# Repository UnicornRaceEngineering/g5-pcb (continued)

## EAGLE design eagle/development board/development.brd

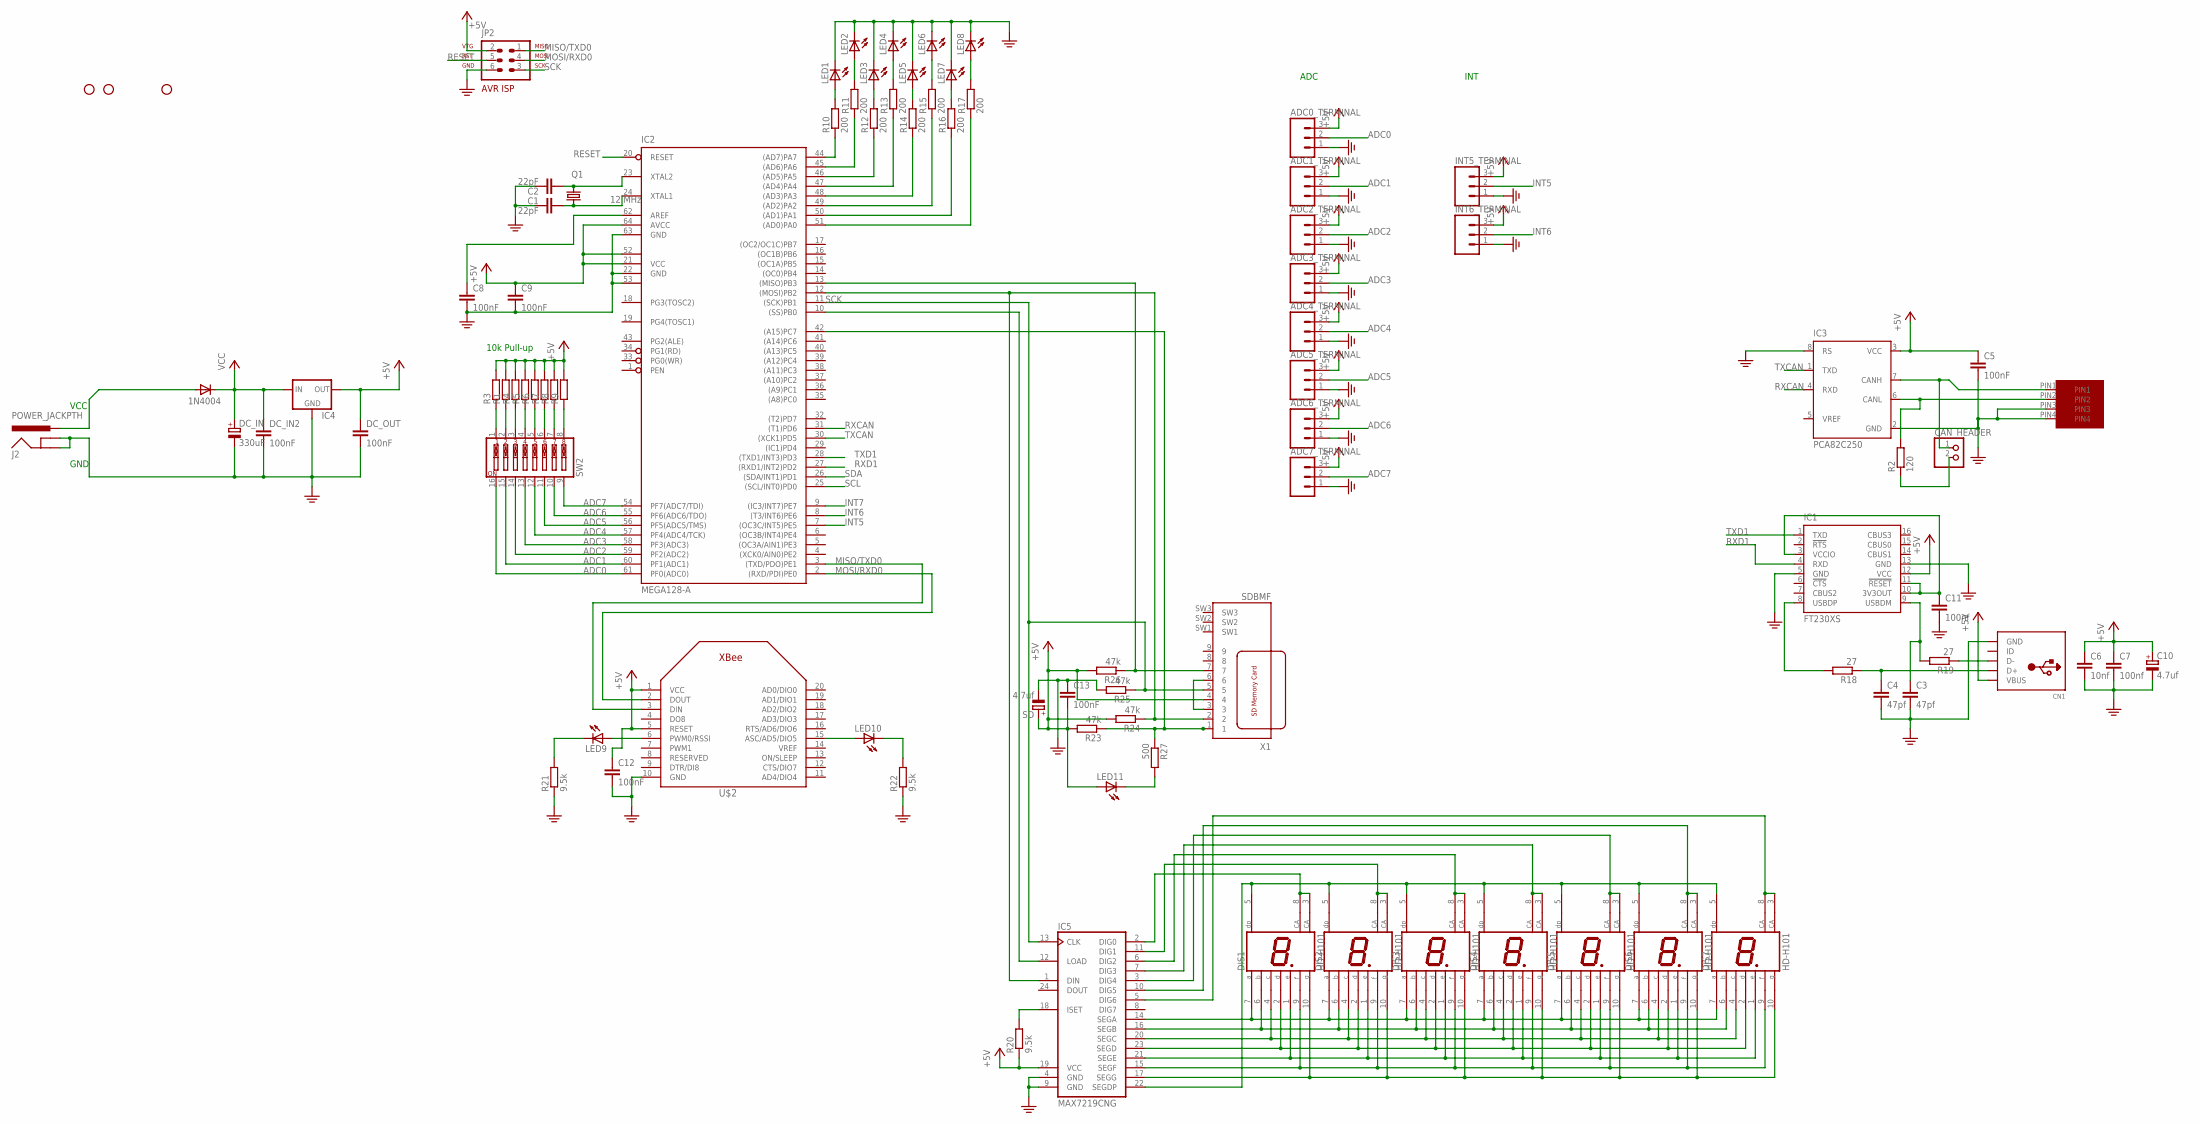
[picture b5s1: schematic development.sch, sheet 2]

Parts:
ADC0_TERMINAL, ADC1_TERMINAL, ADC2_TERMINAL, ADC3_TERMINAL, ADC4_TERMINAL, ADC5_TERMINAL, ADC6_TERMINAL, ADC7_TERMINAL: M03SCREW; SCREWTERMINAL-3.5MM-3
C1, C2: 22pF; C5B2.5
C3, C4: 47pf; C050-025X075
C5, C8, C9, C12, C13: 100nF; C050-024X044
C6: 10nf; C050-025X075
C7, C11: 100nf; C050-025X075
C10: 4.7uf; E2,5-7
CAN_HEADER: PINHD-1X2; 1X02
CN1: USBMINIB; USB-MINIB
DC_IN: 330uF; E15-5
DC_IN2: 100nF; C050-024X044
DC_OUT: 100nF; C050-024X044
DIS1, DIS2, DIS3, DIS4, DIS5, DIS6, DIS7: HD-H101; HDSP-M
ENSRET: 1N4004; DO41-10
IC1: FT230XS; SSOP16
IC2: MEGA128-A; TQFP64
IC3: PCA82C250; DIL08
IC4: V_REG_78XXSIDE; 78XXL
IC5: MAX7219CNG; DIL24-3
INT5_TERMINAL, INT6_TERMINAL: M03SCREW; SCREWTERMINAL-3.5MM-3
J2: POWER_JACKPTH; POWER_JACK_PTH
JP2: AVR-ISP-6
JP3, JP4, JP6: STAND-OFF
LED1, LED2, LED3, LED4, LED5, LED6, LED7, LED8: LED3MM
LED9, LED10, LED11: LED5MM
Q1: 12 MHz; HC49U70
R1, R3, R4, R5, R6, R7, R8, R9: R-EU_R0603; R0603
R2: 120; R0603
R10, R11, R12, R13, R14, R15, R16, R17: 200; R0603
R18, R19: 27; R0603
R20, R21, R22: 9.5k; 0204/7
R23, R24, R25, R26: 47k; 0204/7
R27: 500; 0204/7
SD: 4.7uf; E15-5
SW2: SW_DIP-8; DIPSWITCH-08
U$1: MICROFIT4; MICROFIT4SOCK
U$2: XBEE
X1: SDBMF; SDBMF-009XXBXX2

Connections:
+5V: ADC0_TERMINAL.3, ADC1_TERMINAL.3, ADC2_TERMINAL.3, ADC3_TERMINAL.3, ADC4_TERMINAL.3, ADC5_TERMINAL.3, ADC6_TERMINAL.3, ADC7_TERMINAL.3, C5.1, C6.1, C7.1, C9.1, C10.+, C13.2, CN1.VBUS, DC_OUT.1, IC1.12 (VCC), IC2.21 (VCC), IC2.52 (VCC1), IC2.64 (AVCC), IC3.3 (VCC), IC4.OUT, IC5.19 (VCC), INT5_TERMINAL.3, INT6_TERMINAL.3, JP2.2, LED11.A, R1.2, R3.2, R4.2, R5.2, R6.2, R7.2, R8.2, R9.2, R20.1, R23.2, R24.2, R26.2, SD.+, X1.4
ADC0: ADC0_TERMINAL.2, IC2.61 (PF0(ADC0)), SW2.16
ADC1: ADC1_TERMINAL.2, IC2.60 (PF1(ADC1)), SW2.15
ADC2: ADC2_TERMINAL.2, IC2.59 (PF2(ADC2)), SW2.14
ADC3: ADC3_TERMINAL.2, IC2.58 (PF3(ADC3)), SW2.13
ADC4: ADC4_TERMINAL.2, IC2.57 (PF4(ADC4/TCK)), SW2.12
ADC5: ADC5_TERMINAL.2, IC2.56 (PF5(ADC5/TMS)), SW2.11
ADC6: ADC6_TERMINAL.2, IC2.55 (PF6(ADC6/TDO)), SW2.10
ADC7: ADC7_TERMINAL.2, IC2.54 (PF7(ADC7/TDI)), SW2.9
CANJUMP1: CAN_HEADER.1, IC3.7 (CANH), U$1.PIN1
CANJUMP2: CAN_HEADER.2, R2.1
INT5: IC2.7 ((OC3C/INT5)PE5), INT5_TERMINAL.2
INT6: IC2.8 ((T3/INT6)PE6), INT6_TERMINAL.2
INT7: IC2.9 ((IC3/INT7)PE7)
MISO/TXD0: IC2.3 ((TXD/PDO)PE1), JP2.1, U$2.3 (DIN)
MOSI/RXD0: IC2.2 ((RXD/PDI)PE0), JP2.4, U$2.2 (DOUT)
unnamed: C1.2, IC2.24 (XTAL1), Q1.1
unnamed: C2.2, IC2.23 (XTAL2), Q1.2
unnamed: R1.1, SW2.2
unnamed: R3.1, SW2.1
unnamed: ENSRET.A, J2.PWR
unnamed: IC2.44 ((AD7)PA7), R10.1
unnamed: R4.1, SW2.3
unnamed: LED1.A, R10.2
unnamed: IC2.45 ((AD6)PA6), R11.1
unnamed: C8.1, IC2.62 (AREF)
unnamed: LED2.A, R11.2
unnamed: IC2.46 ((AD5)PA5), R12.1
unnamed: LED3.A, R12.2
unnamed: R5.1, SW2.4
unnamed: R6.1, SW2.5
unnamed: R7.1, SW2.6
unnamed: R8.1, SW2.7
unnamed: IC2.47 ((AD4)PA4), R13.1
unnamed: LED4.A, R13.2
unnamed: R9.1, SW2.8
unnamed: IC2.48 ((AD3)PA3), R14.1
unnamed: LED5.A, R14.2
unnamed: IC2.49 ((AD2)PA2), R15.1
unnamed: IC2.50 ((AD1)PA1), R16.1
unnamed: LED6.A, R15.2
unnamed: LED7.A, R16.2
unnamed: IC2.51 ((AD0)PA0), R17.1
unnamed: LED8.A, R17.2
unnamed: C3.1, IC1.9 (USBDM), R19.2
unnamed: IC1.8 (USBDP), R18.2
unnamed: C4.1, CN1.D+, R18.1
unnamed: CN1.D-, R19.1
unnamed: DIS1.7 (A), DIS2.7 (A), DIS3.7 (A), DIS4.7 (A), DIS5.7 (A), DIS6.7 (A), DIS7.7 (A), IC5.14 (SEGA)
unnamed: DIS1.6 (B), DIS2.6 (B), DIS3.6 (B), DIS4.6 (B), DIS5.6 (B), DIS6.6 (B), DIS7.6 (B), IC5.16 (SEGB)
unnamed: DIS1.4 (C), DIS2.4 (C), DIS3.4 (C), DIS4.4 (C), DIS5.4 (C), DIS6.4 (C), DIS7.4 (C), IC5.20 (SEGC)
unnamed: C11.1, IC1.3 (VCCIO), IC1.10 (3V3OUT), IC1.11 (!RESET)
unnamed: DIS1.2 (D), DIS2.2 (D), DIS3.2 (D), DIS4.2 (D), DIS5.2 (D), DIS6.2 (D), DIS7.2 (D), IC5.23 (SEGD)
unnamed: DIS1.1 (E), DIS2.1 (E), DIS3.1 (E), DIS4.1 (E), DIS5.1 (E), DIS6.1 (E), DIS7.1 (E), IC5.21 (SEGE)
unnamed: DIS1.9 (F), DIS2.9 (F), DIS3.9 (F), DIS4.9 (F), DIS5.9 (F), DIS6.9 (F), DIS7.9 (F), IC5.15 (SEGF)
unnamed: DIS1.10 (G), DIS2.10 (G), DIS3.10 (G), DIS4.10 (G), DIS5.10 (G), DIS6.10 (G), DIS7.10 (G), IC5.17 (SEGG)
unnamed: DIS1.5 (DP), DIS2.5 (DP), DIS3.5 (DP), DIS4.5 (DP), DIS5.5 (DP), DIS6.5 (DP), DIS7.5 (DP), IC5.22 (SEGDP)
unnamed: DIS1.3 (CA), DIS1.8 (CA), IC5.2 (DIG0)
unnamed: DIS2.3 (CA), DIS2.8 (CA), IC5.11 (DIG1)
unnamed: DIS3.3 (CA), DIS3.8 (CA), IC5.6 (DIG2)
unnamed: DIS4.3 (CA), DIS4.8 (CA), IC5.7 (DIG3)
unnamed: DIS5.3 (CA), DIS5.8 (CA), IC5.3 (DIG4)
unnamed: DIS6.3 (CA), DIS6.8 (CA), IC5.10 (DIG5)
unnamed: DIS7.3 (CA), DIS7.8 (CA), IC5.5 (DIG6)
unnamed: LED9.K (C), R21.2
unnamed: IC5.18 (ISET), R20.2
unnamed: IC3.6 (CANL), R2.2, U$1.PIN2
unnamed: LED9.A, U$2.6 (PWM0/RSSI)
unnamed: IC2.10 ((SS)PB0), IC5.12 (LOAD)
unnamed: LED10.A, U$2.15 (ASC/AD5/DIO5)
unnamed: LED10.K (C), R22.2
unnamed: X1.3, X1.6
unnamed: IC2.42 ((A15)PC7), R23.1, R27.1, X1.1
unnamed: IC2.12 ((MOSI)PB2), IC5.1 (DIN), R24.1, X1.2
unnamed: IC2.13 ((MISO)PB3), R26.1, X1.7
unnamed: LED11.K (C), R27.2
PE: ADC0_TERMINAL.1, ADC1_TERMINAL.1, ADC2_TERMINAL.1, ADC3_TERMINAL.1, ADC4_TERMINAL.1, ADC5_TERMINAL.1, ADC6_TERMINAL.1, ADC7_TERMINAL.1, C1.1, C2.1, C3.2, C4.2, C5.2, C6.2, C7.2, C8.2, C9.2, C10.-, C11.2, C12.2, C13.1, CN1.GND, DC_IN.-, DC_IN2.2, DC_OUT.2, IC1.5 (GND), IC1.13 (GND), IC2.22 (GND), IC2.53 (GND1), IC2.63 (GND), IC3.2 (GND), IC3.8 (RS), IC4.GND, IC5.4 (GND), IC5.9 (GND), INT5_TERMINAL.1, INT6_TERMINAL.1, J2.GND, J2.GNDBREAK, JP2.6, LED1.K (C), LED2.K (C), LED3.K (C), LED4.K (C), LED5.K (C), LED6.K (C), LED7.K (C), LED8.K (C), R21.1, R22.1, R25.2, SD.-, U$1.PIN3, U$1.PIN4, U$2.10 (GND)
RESET: IC2.20 (RESET), JP2.5
RXCAN: IC2.31 ((T1)PD6), IC3.4 (RXD)
RXD1: IC1.4 (RXD), IC2.27 ((RXD1/INT2)PD2)
SCK: IC2.11 ((SCK)PB1), IC5.13 (CLK), JP2.3, R25.1, X1.5
SCL: IC2.25 ((SCL/INT0)PD0)
SDA: IC2.26 ((SDA/INT1)PD1)
TXCAN: IC2.30 ((XCK1)PD5), IC3.1 (TXD)
TXD1: IC1.1 (TXD), IC2.28 ((TXD1/INT3)PD3)
VCC: C12.1, DC_IN.+, DC_IN2.1, ENSRET.C, IC4.IN, U$2.1 (VCC), U$2.5 (RESET)

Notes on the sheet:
VCC
GND
ADC
INT
10k Pull-up

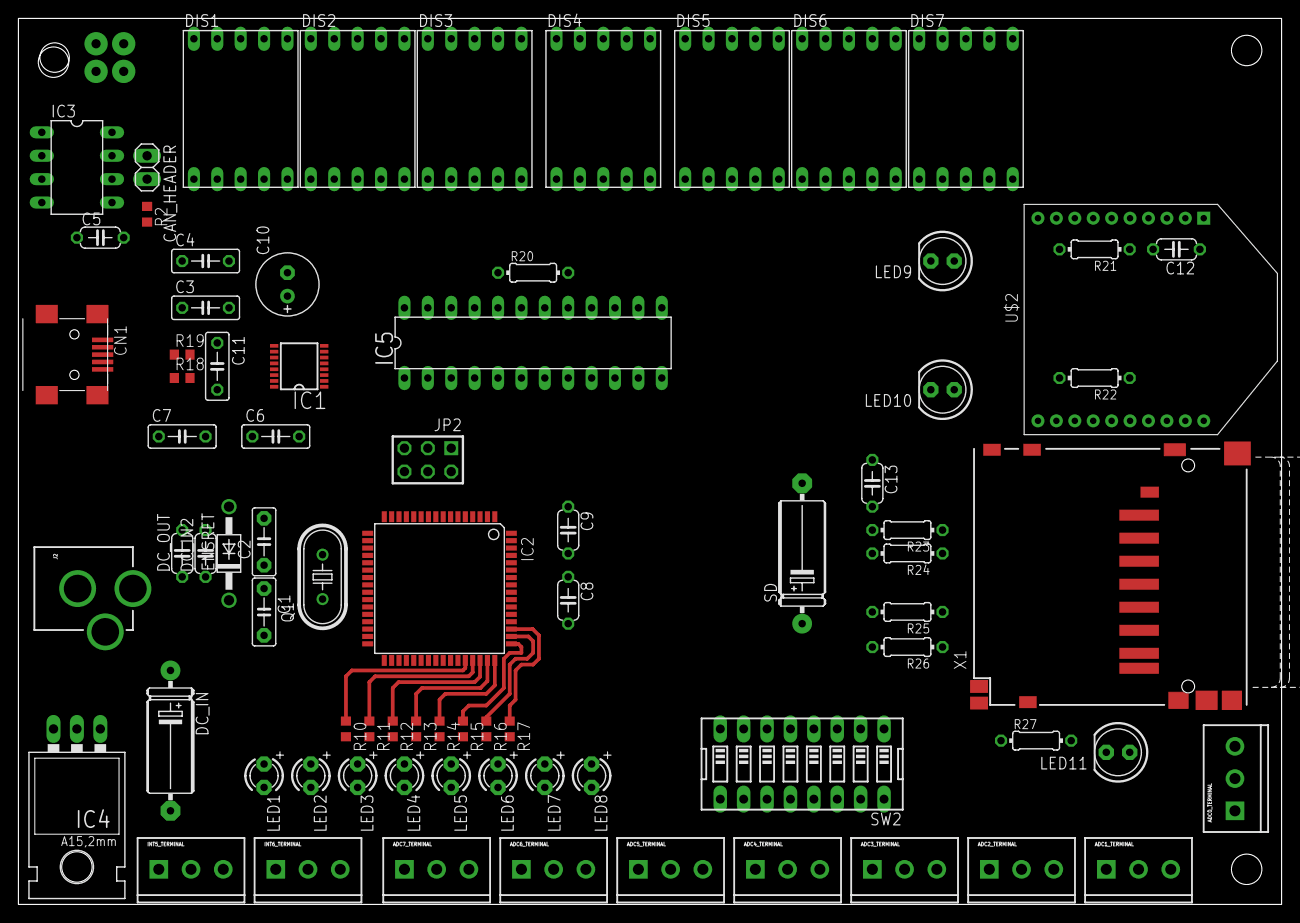
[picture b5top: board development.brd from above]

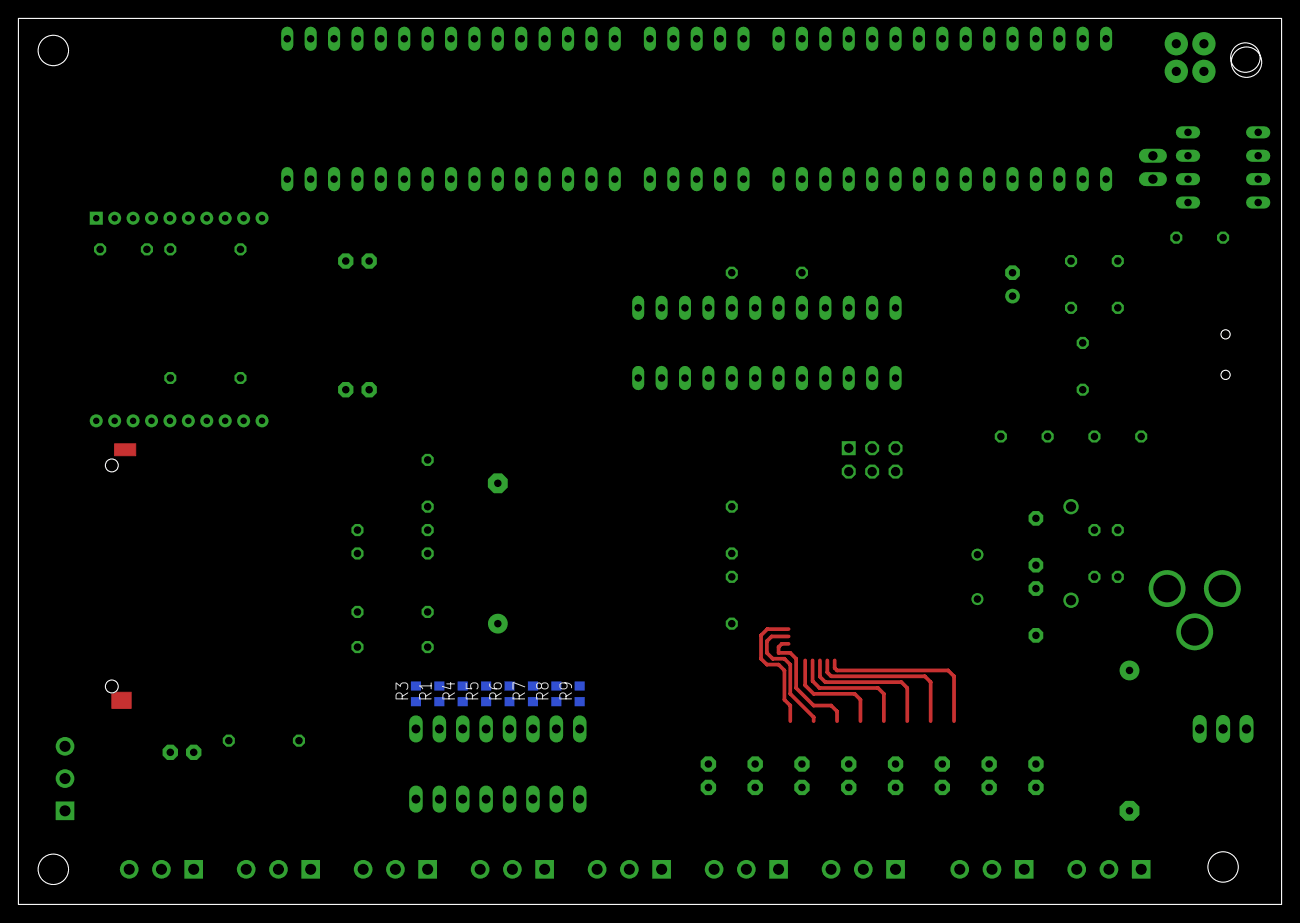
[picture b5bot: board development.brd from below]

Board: 2 copper layers, 137.1 x 96.2 mm, 90 parts (8 on the bottom side), 83 nets.
